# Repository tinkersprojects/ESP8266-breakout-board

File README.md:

# ESP8266-breakout-board
[https://tinkersprojects.com/](https://tinkersprojects.com/)

This is one  PCB for:
- ESP01
- ESP02
- ESP05
- ESP07
- ESP10
- ESP11
- ESP12

The PCB uses headers to connect to a breadboard. The PCB also has resistors, buttons and a programming port to make it easier for you to develop your applications or gadget.

The PCB can be purchased from [https://tinkersprojects.com/product/esp2688-breakout/](https://tinkersprojects.com/product/esp2688-breakout/)

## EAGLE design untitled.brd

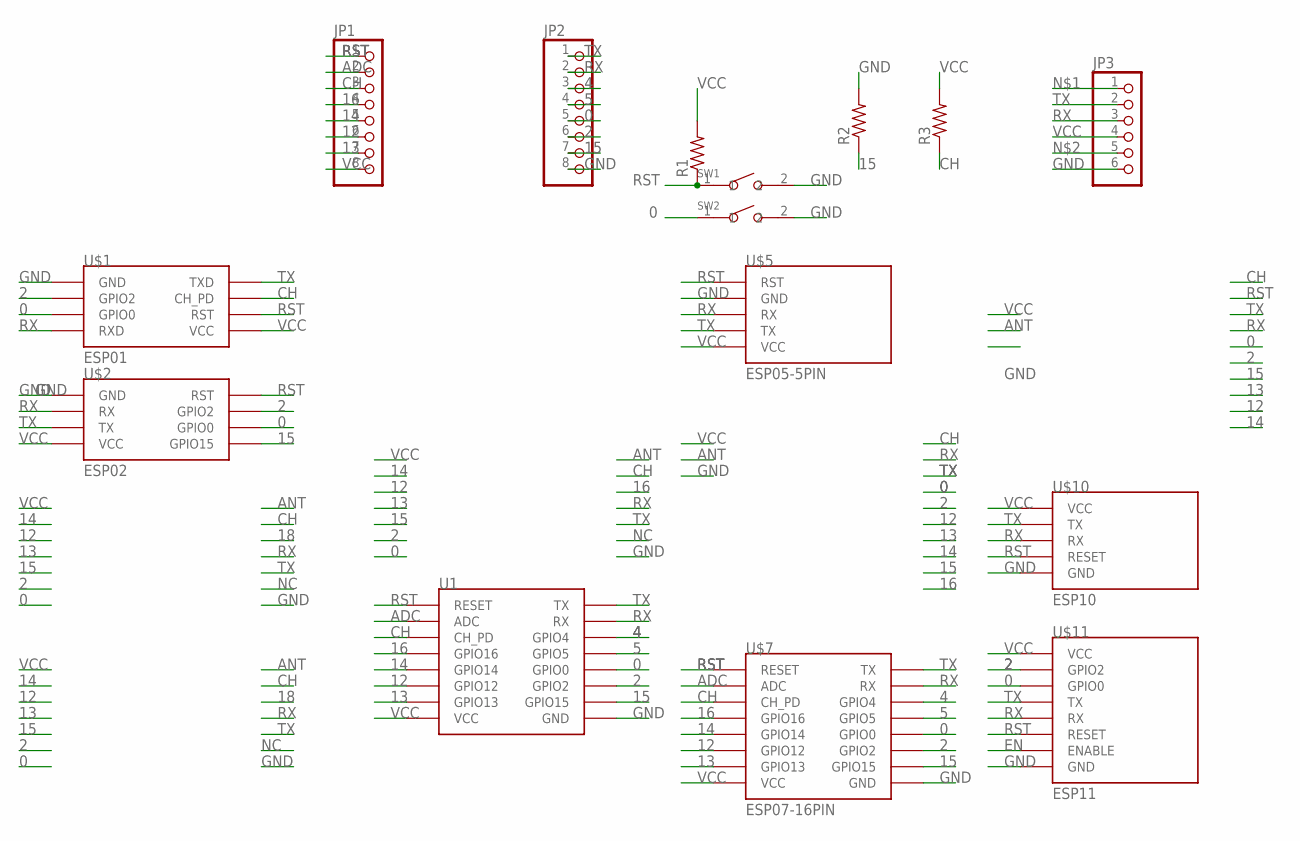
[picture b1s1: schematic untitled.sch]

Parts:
JP1, JP2: PINHD-1X8; 1X08
JP3: PINHD-1X6; 1X06
R1, R2, R3: RESISTOR1206; 1206
SW1, SW2: SMD-BUTTON(2P-6.0X3.0X2.5MM)-DHT-1163S; SW2-4.0-6.0X3.0X2.5MM
U1: ESP12SMD; ESP12-SMD
U$1: ESP01
U$2: ESP02
U$5: ESP05-5PIN
U$7: ESP07-16PIN
U$10: ESP10
U$11: ESP11

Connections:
0: JP2.5, SW2.1, U1.GPIO0, U$1.GPIO0, U$2.GPIO0, U$7.GPIO0, U$11.P$6 (GPIO0)
2: JP2.6, U1.GPIO2, U$1.GPIO2, U$2.GPIO2, U$7.GPIO2, U$11.P$7 (GPIO2)
4: JP2.3, U1.GPIO4, U$7.GPIO4
5: JP2.4, U1.GPIO5, U$7.GPIO5
12: JP1.6, U1.GPIO12, U$7.GPIO12
13: JP1.7, U1.GPIO13, U$7.GPIO13
14: JP1.5, U1.GPIO14, U$7.GPIO14
15: JP2.7, R2.1, U1.GPIO15, U$2.GPIO15/POWERDOWN (GPIO15), U$7.GPIO15
16: JP1.4, U1.GPIO16, U$7.GPIO16
ADC: JP1.2, U1.ADC, U$7.ADC
CH: JP1.3, R3.1, U1.CH_PD, U$1.CH_PD, U$7.CH_PD
EN: U$11.P$2 (ENABLE)
GND: JP2.8, JP3.6, R2.2, SW1.2, SW2.2, U1.GND, U$1.GND, U$2.GND, U$5.GND, U$7.GND, U$10.GND, U$11.P$1 (GND)
RST: JP1.1, R1.1, SW1.1, U1.RESET, U$1.RST, U$2.RST, U$5.RST, U$7.REST (RESET), U$10.RESET, U$11.P$3 (RESET)
RX: JP2.2, JP3.3, U1.RXD0 (RX), U$1.RX (RXD), U$2.RX, U$5.RX, U$7.RX, U$10.RX, U$11.P$4 (RX)
TX: JP2.1, JP3.2, U1.TXD0 (TX), U$1.TX (TXD), U$2.TX, U$5.TX, U$7.TX, U$10.TX, U$11.P$5 (TX)
VCC: JP1.8, JP3.4, R1.2, R3.2, U1.VCC, U$1.VCC, U$2.VCC, U$5.VCC, U$7.VCC, U$10.VCC, U$11.P$8 (VCC)

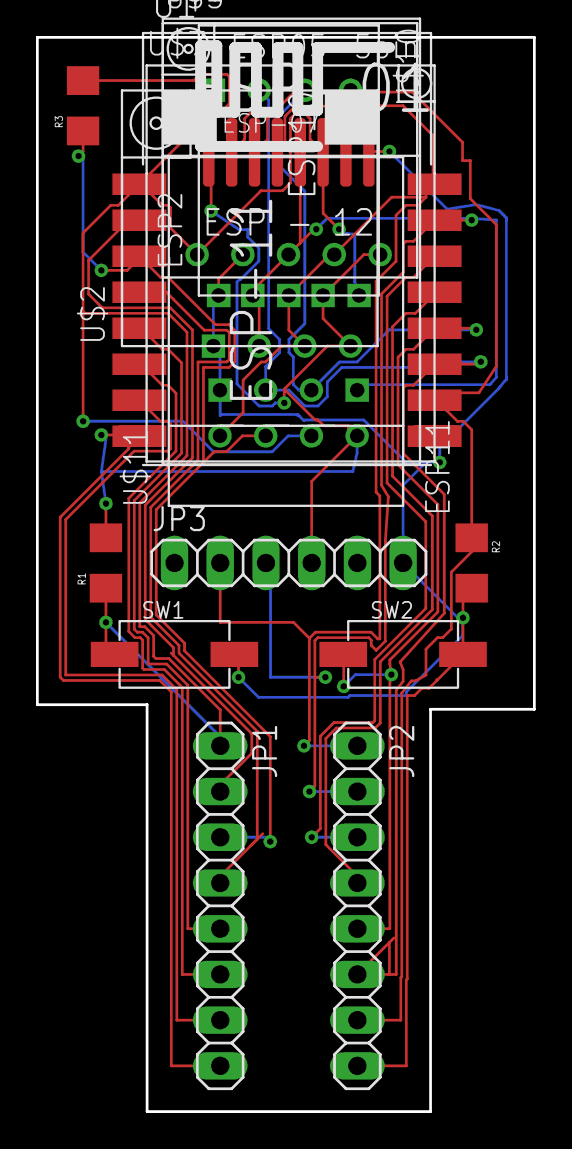
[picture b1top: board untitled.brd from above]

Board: 2 copper layers, 27.6 x 59.7 mm, 15 parts (0 on the bottom side), 16 nets.

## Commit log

2018-04-11 Add files via upload
    Upload files
2018-04-12 Update README.md
    Update read me

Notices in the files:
parts and their libraries:
SparkFun-Resistors: Licensing: Creative Commons ShareAlike 4.0 International - https://creativecommons.org/licenses/by-sa/4.0
